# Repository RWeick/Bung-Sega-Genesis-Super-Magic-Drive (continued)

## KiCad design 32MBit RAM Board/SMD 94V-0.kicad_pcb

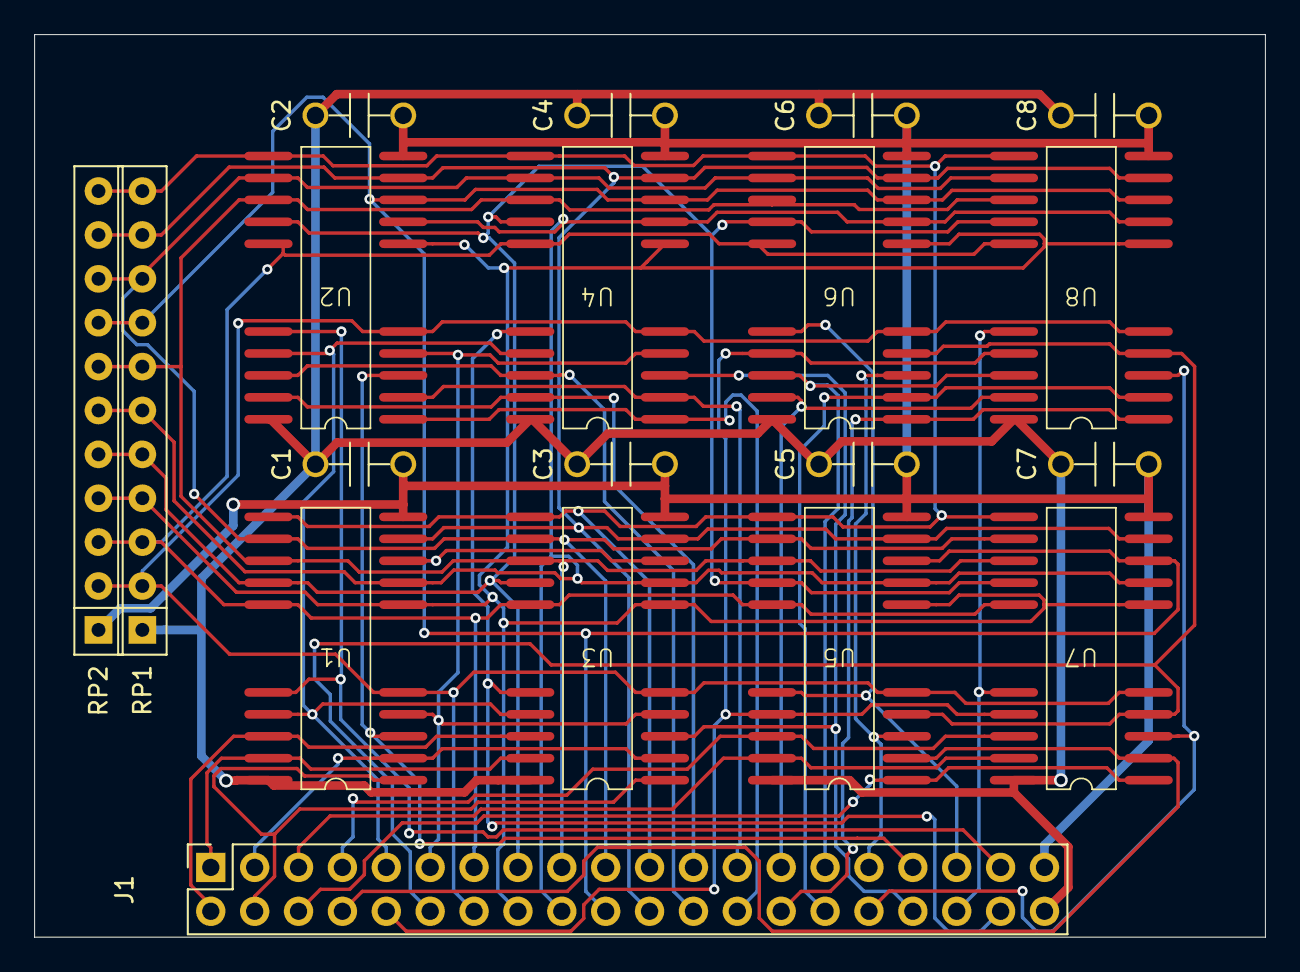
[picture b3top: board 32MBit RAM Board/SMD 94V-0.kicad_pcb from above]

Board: 2 copper layers, 71.3 x 52.2 mm, 19 parts (0 on the bottom side), 40 nets.

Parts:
C1, C2, C3, C4, C5, C6, C7, C8: 100 nF; Capacitor
J1: Conn_02x20_Odd_Even; PinHeader_2x20_P2.54mm_Vertical
RP1, RP2: R_Network10; R_Array_SIP11
U1, U2, U3, U4, U5, U6, U7, U8: KM44C1000ALJ-7

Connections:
/A0: J1.16, RP1.4 (R3), RP2.4 (R3), U1.6 (A0), U2.6 (A0), U3.6 (A0), U4.6 (A0), U5.6 (A0), U6.6 (A0), U7.6 (A0), U8.6 (A0)
/A1: J1.18, RP1.6 (R5), RP2.6 (R5), U1.7 (A1), U2.7 (A1), U3.7 (A1), U4.7 (A1), U5.7 (A1), U6.7 (A1), U7.7 (A1), U8.7 (A1)
/A2: J1.20, RP1.8 (R7), RP2.8 (R7), U1.8 (A2), U2.8 (A2), U3.8 (A2), U4.8 (A2), U5.8 (A2), U6.8 (A2), U7.8 (A2), U8.8 (A2)
/A3: J1.22, RP1.10 (R9), RP2.10 (R9), U1.9 (A3), U2.9 (A3), U3.9 (A3), U4.9 (A3), U5.9 (A3), U6.9 (A3), U7.9 (A3), U8.9 (A3)
/A4: J1.21, RP1.11 (R10), RP2.11 (R10), U1.11 (A4), U2.11 (A4), U3.11 (A4), U4.11 (A4), U5.11 (A4), U6.11 (A4), U7.11 (A4), U8.11 (A4)
/A5: J1.19, RP1.9 (R8), RP2.9 (R8), U1.12 (A5), U2.12 (A5), U3.12 (A5), U4.12 (A5), U5.12 (A5), U6.12 (A5), U7.12 (A5), U8.12 (A5)
/A6: J1.17, RP1.7 (R6), RP2.7 (R6), U1.13 (A6), U2.13 (A6), U3.13 (A6), U4.13 (A6), U5.13 (A6), U6.13 (A6), U7.13 (A6), U8.13 (A6)
/A7: J1.15, RP1.5 (R4), RP2.5 (R4), U1.14 (A7), U2.14 (A7), U3.14 (A7), U4.14 (A7), U5.14 (A7), U6.14 (A7), U7.14 (A7), U8.14 (A7)
/A8: J1.13, RP1.3 (R2), RP2.3 (R2), U1.15 (A8), U2.15 (A8), U3.15 (A8), U4.15 (A8), U5.15 (A8), U6.15 (A8), U7.15 (A8), U8.15 (A8)
/A9: J1.14, RP1.2 (R1), RP2.2 (R1), U1.5 (A9), U2.5 (A9), U3.5 (A9), U4.5 (A9), U5.5 (A9), U6.5 (A9), U7.5 (A9), U8.5 (A9)
/GND: C1.1, C2.1, C3.1, C4.1, C5.1, C6.1, C7.1, C8.1, J1.40, RP1.1 (common), U1.20 (GND), U2.20 (GND), U3.20 (GND), U4.20 (GND), U5.20 (GND), U6.20 (GND), U7.20 (GND), U8.20 (GND)
/U1-4.~CAS: J1.9, U1.17 (~CAS), U2.17 (~CAS), U3.17 (~CAS), U4.17 (~CAS)
/U1-4.~RAS: J1.11, U1.4 (~RAS), U2.4 (~RAS), U3.4 (~RAS), U4.4 (~RAS)
/U1-U2.~OE: J1.37, U1.16 (~OE), U2.16 (~OE)
/U1-U2.~W: J1.33, U1.3 (~W), U2.3 (~W)
/U1-U3.DQ0: J1.4, U1.1 (DQ0), U3.1 (DQ0)
/U1-U3.DQ1: J1.3, U1.2 (DQ1), U3.2 (DQ1)
/U1-U3.DQ2: J1.2, U1.18 (DQ2), U3.18 (DQ2)
/U1-U3.DQ3: J1.1, U1.19 (DQ3), U3.19 (DQ3)
/U2-U4.DQ0: J1.26, U2.1 (DQ0), U4.1 (DQ0)
/U2-U4.DQ1: J1.25, U2.2 (DQ1), U4.2 (DQ1)
/U2-U4.DQ2: J1.24, U2.18 (DQ2), U4.18 (DQ2)
/U2-U4.DQ3: J1.23, U2.19 (DQ3), U4.19 (DQ3)
/U3-U4.~OE: J1.38, U3.16 (~OE), U4.16 (~OE)
/U3-U4.~W: J1.34, U3.3 (~W), U4.3 (~W)
/U5-8.~CAS: J1.10, U5.17 (~CAS), U6.17 (~CAS), U7.17 (~CAS), U8.17 (~CAS)
/U5-8.~RAS: J1.12, U5.4 (~RAS), U6.4 (~RAS), U7.4 (~RAS), U8.4 (~RAS)
/U5-U6.~OE: J1.35, U5.16 (~OE), U6.16 (~OE)
/U5-U6.~W: J1.31, U5.3 (~W), U6.3 (~W)
/U5-U7.DQ0: J1.6, U5.1 (DQ0), U7.1 (DQ0)
/U5-U7.DQ1: J1.8, U5.2 (DQ1), U7.2 (DQ1)
/U5-U7.DQ2: J1.7, U5.18 (DQ2), U7.18 (DQ2)
/U5-U7.DQ3: J1.5, U5.19 (DQ3), U7.19 (DQ3)
/U6-U8.DQ0: J1.28, U6.1 (DQ0), U8.1 (DQ0)
/U6-U8.DQ1: J1.30, U6.2 (DQ1), U8.2 (DQ1)
/U6-U8.DQ2: J1.29, U6.18 (DQ2), U8.18 (DQ2)
/U6-U8.DQ3: J1.27, U6.19 (DQ3), U8.19 (DQ3)
/U7-U8.~OE: J1.36, U7.16 (~OE), U8.16 (~OE)
/U7-U8.~W: J1.32, U7.3 (~W), U8.3 (~W)
/VCC: C1.2, C2.2, C3.2, C4.2, C5.2, C6.2, C7.2, C8.2, J1.39, RP2.1 (common), U1.10 (VCC), U2.10 (VCC), U3.10 (VCC), U4.10 (VCC), U5.10 (VCC), U6.10 (VCC), U7.10 (VCC), U8.10 (VCC)

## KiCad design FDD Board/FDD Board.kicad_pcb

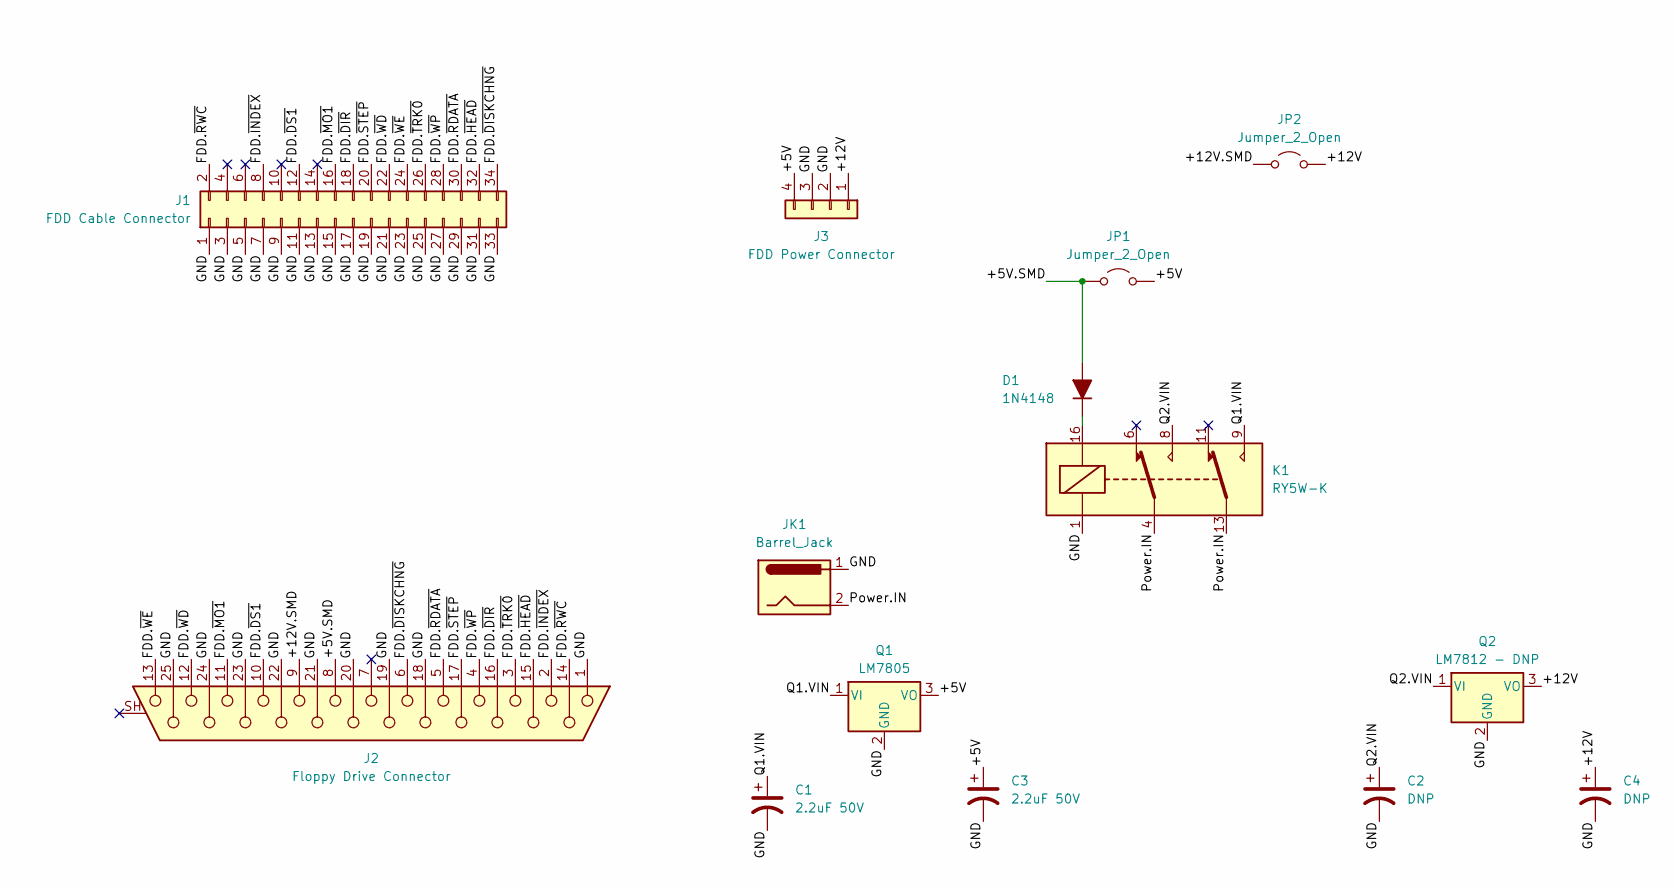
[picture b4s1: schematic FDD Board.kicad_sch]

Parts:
C1: 2.2uF 50V; CP_Radial_D6.3mm_P2.50mm
C2: DNP; CP_Radial_D6.3mm_P2.50mm
C3: 2.2uF 50V; CP_Radial_D10.0mm_P5.00mm
C4: DNP; CP_Radial_D10.0mm_P5.00mm
D1: 1N4148; Diode
J1: FDD Cable Connector; PinHeader_2x17_P2.54mm_Vertical
J2: Floppy Drive Connector; DSUB-25_Socket_Horizontal_P2.77x2.84mm_EdgePinOffset7.70mm_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
J3: FDD Power Connector; FDD Power
JK1: Barrel_Jack; BarrelJack_Horizontal
JP1, JP2: Jumper_2_Open; PinHeader_1x02_P2.54mm_Vertical
K1: RY5W-K; Relay_DPDT_Omron_G5V-2
Q1: LM7805; TO-220-3_Vertical
Q2: LM7812 - DNP; TO-220-3_Vertical

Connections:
/+5V: C3.1, J3.4, JP1.2 (B), Q1.3 (VO)
/+5V.SMD: D1.2 (A), J2.8, JP1.1 (A)
/+12V: C4.1, J3.1, JP2.2 (B), Q2.3 (VO)
/+12V.SMD: J2.9, JP2.1 (A)
/FDD.~DIR: J1.18, J2.16
/FDD.~DISKCHNG: J1.34, J2.6
/FDD.~DS1: J1.12, J2.10
/FDD.~HEAD: J1.32, J2.15
/FDD.~INDEX: J1.8, J2.2
/FDD.~MO1: J1.16, J2.11
/FDD.~RDATA: J1.30, J2.5
/FDD.~RWC: J1.2, J2.14
/FDD.~STEP: J1.20, J2.17
/FDD.~TRK0: J1.26, J2.3
/FDD.~WD: J1.22, J2.12
/FDD.~WE: J1.24, J2.13
/FDD.~WP: J1.28, J2.4
/GND: C1.2, C2.2, C3.2, C4.2, J1.1, J1.3, J1.5, J1.7, J1.9, J1.11, J1.13, J1.15, J1.17, J1.19, J1.21, J1.23, J1.25, J1.27, J1.29, J1.31, J1.33, J2.1, J2.18, J2.19, J2.20, J2.21, J2.22, J2.23, J2.24, J2.25, J3.2, J3.3, JK1.1, K1.1, Q1.2 (GND), Q2.2 (GND)
/Power.IN: JK1.2, K1.4, K1.13
/Q1.VIN: C1.1, K1.9, Q1.1 (VI)
/Q2.VIN: C2.1, K1.8, Q2.1 (VI)
unnamed: D1.1 (K), K1.16

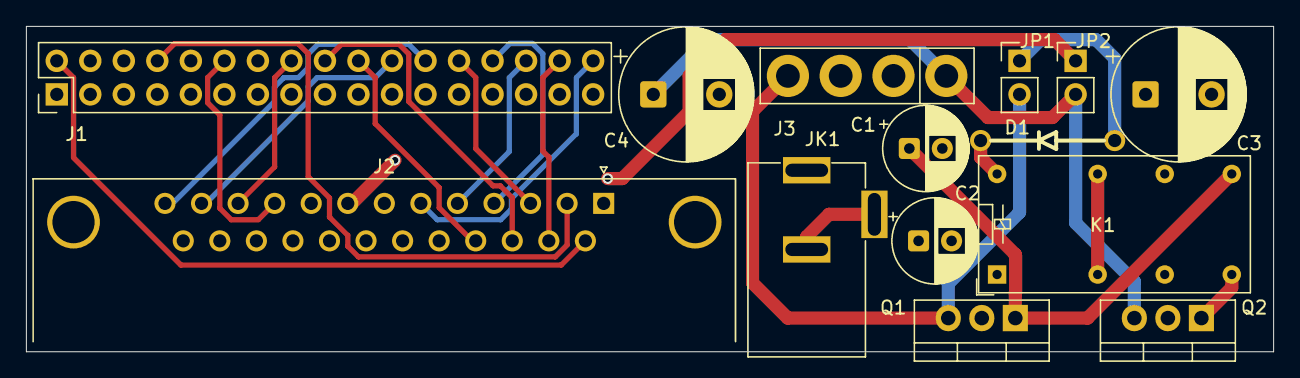
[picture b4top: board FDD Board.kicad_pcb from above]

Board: 4 copper layers, 94.5 x 24.7 mm, 14 parts (0 on the bottom side), 22 nets.
